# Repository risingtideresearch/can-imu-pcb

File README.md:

# CAN IMU

A carrier PCB for a Microstrain 3DM-CV7 Inertial Measurement Unit to act as a CAN / NMEA 2000
device.

It is designed to fit in the Hammond [1554E2GY](https://www.hammfg.com/part/1554E2GY) enclosure.

## Assembly

The BOM can be found [here](output/CAN_IMU_rev1_BOM.csv), and includes most parts, but there are
some additional parts not included there:

- The case: Hammond 1554E2GY
- Brass solderable nuts for securing the microstrain: SMTSOB-256-2ET (qty 3)
- M3x8 screws for securing the PCB in the enclosure (These should ideally be non-ferrous if you care about magnetemeter accuracy) 
- M12 connector: [T4130012051-000](https://www.digikey.com/en/products/detail/te-connectivity-amp-connectors/T4130012051-000/7927438)
- 5-pin PH connector housing for wiring the M12 to the board:
  [PHR-5](https://www.digikey.com/en/products/detail/jst-sales-america-inc/PHR-5/608605) (plus the
  appropriate crimp pins or pre-crimped wires)

## Software

Software for this board can be found in the [can-imu-fw repo](https://github.com/risingtideresearch/can-imu-fw)

# Revision History

## Rev 1

First fabricated January 2026. 

### Errata

- The microstrain IMU connector is backwards (repairable with cut traces and bodge wires)

## Rev 2

Fixes IMU connector pinout. No CPU pin changes, and functionally equivalent to bodged rev1.

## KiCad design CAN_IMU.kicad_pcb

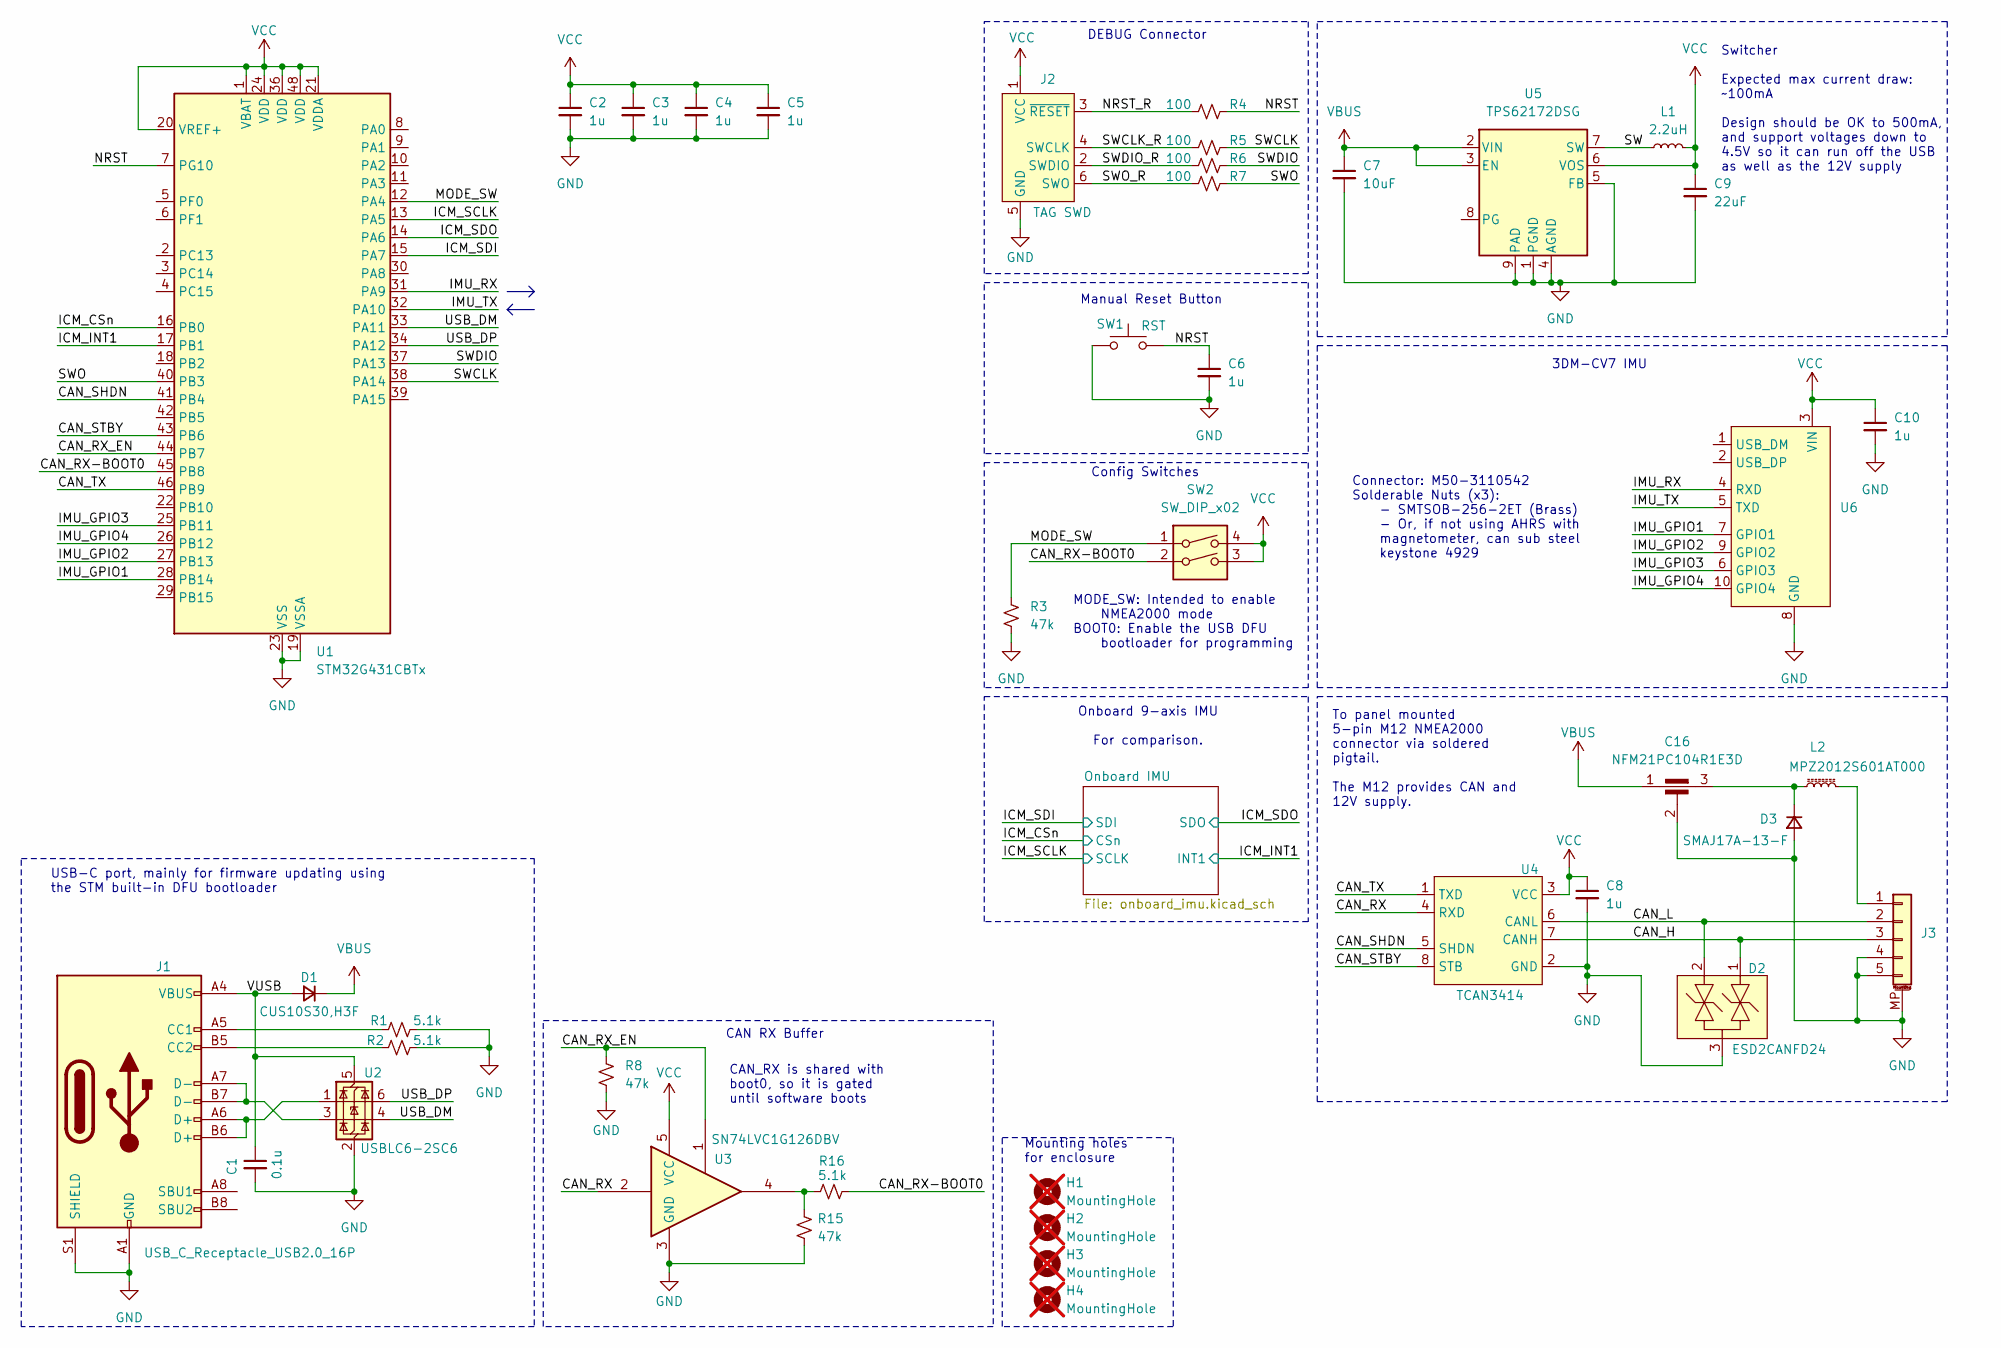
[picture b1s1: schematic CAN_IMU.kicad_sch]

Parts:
C1: 0.1u; C_0603_1608Metric; Mfg Part Number CL10B104KA8NNNC; LCSC Part Number C1590
C2, C3, C4, C5, C6, C8, C10: 1u; C_0603_1608Metric; Mfg Part Number CL10B105KP8NNNC; Digikey Part Number 1276-1946-1-ND
C7: 10uF; C_0805_2012Metric; Mfg Part Number GRM21BR61H106KE43L; Digikey Part Number 490-18663-1-ND
C9: 22uF; C_1206_3216Metric; Mfg Part Number CL31A226KAHNNNE; Digikey Part Number 1276-3047-1-ND
C16: NFM21PC104R1E3D; NFM21PC_Feedthrough_Cap; Mfg Part Number NFM21PC104R1E3D; LCSC Part Number C86150
D1: CUS10S30,H3F; D_SOD-323_HandSoldering; Mfg Part Number CUS10S30,H3F; Digikey Part Number CUS10S30H3FCT-ND
D2: ESD2CANFD24; SOT-23; Mfg Part Number ESD2CANFD24; Digikey Part Number 1727-PESD2CANFD24UU-QXCT-ND
D3: SMAJ17A-13-F; D_SMA; Mfg Part Number SMAJ17A-13-F; Digikey Part Number SMAJ17A-FDICT-ND
H1, H2, H3, H4: MountingHole; MountingHole_3.2mm_M3; not fitted
J1: USB_C_Receptacle_USB2.0_16P; USB_C_Receptacle_JAE_DX07S024WJ3R400; Mfg Part Number DX07S024WJ3R400; Digikey Part Number 670-2950-1-ND
J2: TAG SWD; Tag-Connect_TC2030-IDC-FP_2x03_P1.27mm_Vertical
J3: Conn_01x05; JST_PH_B5B-PH-SM4-TB_1x05-1MP_P2.00mm_Vertical; Mfg Part Number B5B-PH-SM4-TB; Digikey Part Number 455-B5B-PH-SM4-TBCT-ND
L1: 2.2uH; IND_LQH5BPN2R2NT0L; Mfg Part Number LQH5BPN2R2NT0L; Digikey Part Number 490-7778-1-ND
L2: MPZ2012S601AT000; L_0805_2012Metric; Mfg Part Number MPZ2012S601AT000; Digikey Part Number 445-MPZ2012S601AT000CT-ND
R1, R2, R16: 5.1k; R_0603_1608Metric; Mfg Part Number RC0603FR-075K1L; LCSC Part Number C105580
R3, R8, R15: 47k; R_0603_1608Metric; Mfg Part Number RC0603FR-0747KL; Digikey Part Number 311-47.0KHRCT-ND
R4, R5, R6, R7: 100; R_0603_1608Metric; Mfg Part Number RC0603FR-07100RL; Digikey Part Number 311-100HRCT-ND
SW1: RST; SW_SPST_PTS810; Mfg Part Number PTS810SJK250SMTRLFS; LCSC Part Number C221896
SW2: SW_DIP_x02; SW_DIP_SPSTx02_Slide_6.7x6.64mm_W8.61mm_P2.54mm_LowProfile; Mfg Part Number DS04-254-2-02BK-SMT-TR; Digikey Part Number 2223-DS04-254-2-02BK-SMT-CT-ND
U1: STM32G431CBTx; LQFP-48_7x7mm_P0.5mm; Mfg Part Number STM32G431CBT6; Digikey Part Number 497-19473-ND
U2: USBLC6-2SC6; SOT-23-6; Mfg Part Number USBLC6-2SC6; LCSC Part Number C7519
U3: SN74LVC1G126DBV; SOT-23-5; Mfg Part Number SN74LVC1G126DBVR; Digikey Part Number 296-11605-1-ND
U4: TCAN3414; SOIC-8_3.9x4.9mm_P1.27mm; Mfg Part Number TCAN3414DR; Digikey Part Number 296-TCAN3414DRCT-ND
U5: TPS62172DSG; WSON-8-1EP_2x2mm_P0.5mm_EP0.9x1.6mm_ThermalVias; Mfg Part Number TPS62172DSGR; Digikey Part Number 296-39449-1-ND
U6: 3DM-CV7; Mfg Part Number M50-3110542; Digikey Part Number 952-2342-ND

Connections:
/CAN_H: D2.1, J3.3, U4.7 (CANH)
/CAN_L: D2.2, J3.2, U4.6 (CANL)
/CAN_RX: U3.2, U4.4 (RXD)
/CAN_RX-BOOT0: R16.1, SW2.2, U1.45 (PB8)
/CAN_RX_EN: R8.1, U1.44 (PB7), U3.1
/CAN_SHDN: U1.41 (PB4), U4.5 (SHDN)
/CAN_STBY: U1.43 (PB6), U4.8 (STB)
/CAN_TX: U1.46 (PB9), U4.1 (TXD)
/ICM_CSn: U1.16 (PB0); also elsewhere on the board
/ICM_INT1: U1.17 (PB1); also elsewhere on the board
/ICM_SCLK: U1.13 (PA5); also elsewhere on the board
/ICM_SDI: U1.15 (PA7); also elsewhere on the board
/ICM_SDO: U1.14 (PA6); also elsewhere on the board
/IMU_GPIO1: U1.28 (PB14), U6.7 (GPIO1)
/IMU_GPIO2: U1.27 (PB13), U6.9 (GPIO2)
/IMU_GPIO3: U1.25 (PB11), U6.6 (GPIO3)
/IMU_GPIO4: U1.26 (PB12), U6.10 (GPIO4)
/IMU_RX: U1.31 (PA9), U6.4 (RXD)
/IMU_TX: U1.32 (PA10), U6.5 (TXD)
/MODE_SW: R3.1, SW2.1, U1.12 (PA4)
/NRST: C6.1, R4.1, SW1.2, U1.7 (PG10)
/NRST_R: J2.3 (~RESET), R4.2
/SW: L1.1, U5.7 (SW)
/SWCLK: R5.1, U1.38 (PA14)
/SWCLK_R: J2.4 (SWCLK), R5.2
/SWDIO: R6.1, U1.37 (PA13)
/SWDIO_R: J2.2 (SWDIO), R6.2
/SWO: R7.1, U1.40 (PB3)
/SWO_R: J2.6 (SWO), R7.2
/USB_DM: U1.33 (PA11), U2.4 (I/O2)
/USB_DP: U1.34 (PA12), U2.6 (I/O1)
/VUSB: C1.1, D1.2 (A), J1.A4 (VBUS), J1.A9 (VBUS), J1.B4 (VBUS), J1.B9 (VBUS), U2.5 (VBUS)
GND: C1.2, C2.2, C3.2, C4.2, C5.2, C6.2, C7.2, C8.2, C9.2, C10.2, C16.2, D2.3, D3.2 (A), J1.A1 (GND), J1.A12 (GND), J1.B1 (GND), J1.B12 (GND), J1.S1 (SHIELD), J2.5 (GND), J3.4, J3.5, J3.MP (MountPin), R1.1, R2.1, R3.2, R8.2, R15.2, SW1.1, U1.19 (VSSA), U1.23 (VSS), U1.35 (VSS), U1.47 (VSS), U2.2 (GND), U3.3 (GND), U4.2 (GND), U5.1 (PGND), U5.4 (AGND), U5.5 (FB), U5.9 (PAD), U6.8 (GND); also elsewhere on the board
unnamed: C16.3, D3.1 (K), L2.1
unnamed: J1.A5 (CC1), R1.2
unnamed: J1.B5 (CC2), R2.2
unnamed: J1.A6 (D+), J1.B6 (D+), U2.1 (I/O1)
unnamed: J1.A7 (D-), J1.B7 (D-), U2.3 (I/O2)
unnamed: J3.1, L2.2
unnamed: R15.1, R16.2, U3.4
VBUS: C7.1, C16.1, D1.1 (K), U5.2 (VIN), U5.3 (EN)
VCC: C2.1, C3.1, C4.1, C5.1, C8.1, C9.1, C10.1, J2.1 (VCC), L1.2, SW2.3, SW2.4, U1.1 (VBAT), U1.20 (VREF+), U1.21 (VDDA), U1.24 (VDD), U1.36 (VDD), U1.48 (VDD), U3.5 (VCC), U4.3 (VCC), U5.6 (VOS), U6.3 (VIN); also elsewhere on the board

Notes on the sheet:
DEBUG Connector
Mounting holes for enclosure
To panel mounted 5-pin M12 NMEA2000 connector via soldered pigtail. The M12 provides CAN and 12V supply.
Connector: M50-3110542 Solderable Nuts (x3): - SMTSOB-256-2ET (Brass) - Or, if not using AHRS with magnetometer, can sub steel keystone 4929
CAN RX Buffer
3DM-CV7 IMU
Manual Reset Button
Onboard 9-axis IMU For comparison.
CAN_RX is shared with boot0, so it is gated until software boots
MODE_SW: Intended to enable NMEA2000 mode BOOT0: Enable the USB DFU bootloader for programming
Switcher Expected max current draw: ~100mA Design should be OK to 500mA, and support voltages down to 4.5V so it can run off the USB as well as the 12V supply
USB-C port, mainly for firmware updating using the STM built-in DFU bootloader
Config Switches

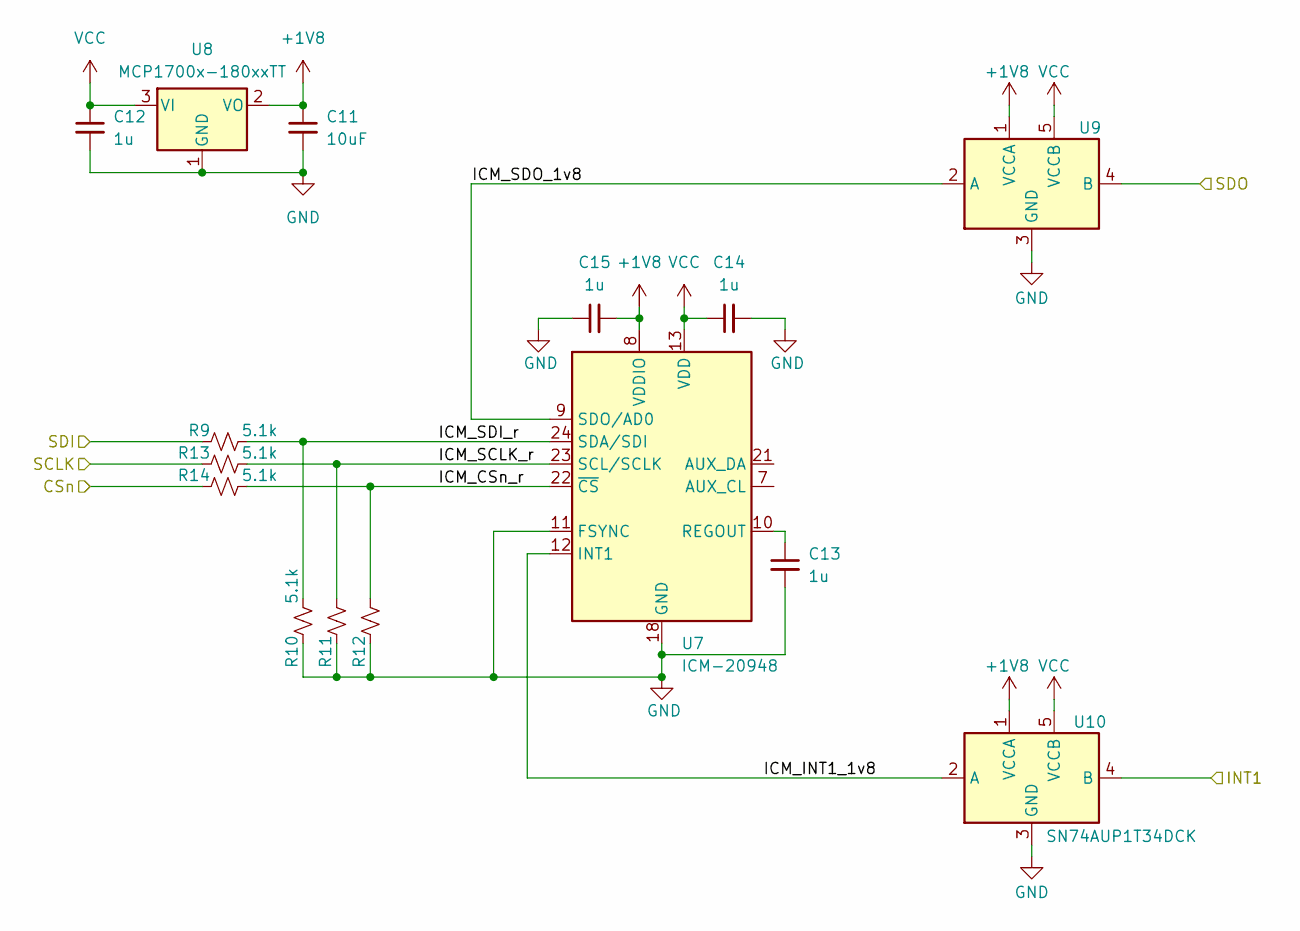
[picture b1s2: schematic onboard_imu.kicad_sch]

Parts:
C11: 10uF; C_0805_2012Metric; Mfg Part Number GRM21BR61H106KE43L; Digikey Part Number 490-18663-1-ND
C12, C13, C14, C15: 1u; C_0603_1608Metric; Mfg Part Number CL10B105KP8NNNC; Digikey Part Number 1276-1946-1-ND
R9, R10, R11, R12, R13, R14: 5.1k; R_0603_1608Metric; Mfg Part Number RC0603FR-075K1L; LCSC Part Number C105580
U7: ICM-20948; InvenSense_QFN-24_3x3mm_P0.4mm; Mfg Part Number ICM-20948; Digikey Part Number 1428-1123-1-ND
U8: MCP1700x-180xxTT; SOT-23; Mfg Part Number MCP1700T-1802E/TT; Digikey Part Number MCP1700T1802ETTCT-ND
U9, U10: SN74AUP1T34DCK; SOT-353_SC-70-5; Mfg Part Number SN74AUP1T34DCKR; Digikey Part Number 296-34900-1-ND

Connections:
+1V8: C11.1, C15.2, U7.8 (VDDIO), U8.2 (VO), U9.1 (VCCA), U10.1 (VCCA)
/ICM_CSn: R14.2; also elsewhere on the board
/ICM_INT1: U10.4 (B); also elsewhere on the board
/ICM_SCLK: R13.2; also elsewhere on the board
/ICM_SDI: R9.2; also elsewhere on the board
/ICM_SDO: U9.4 (B); also elsewhere on the board
/Onboard IMU/ICM_CSn_r: R12.1, R14.1, U7.22 (~CS)
/Onboard IMU/ICM_INT1_1v8: U7.12 (INT1), U10.2 (A)
/Onboard IMU/ICM_SCLK_r: R11.1, R13.1, U7.23 (SCL/SCLK)
/Onboard IMU/ICM_SDI_r: R9.1, R10.1, U7.24 (SDA/SDI)
/Onboard IMU/ICM_SDO_1v8: U7.9 (SDO/AD0), U9.2 (A)
GND: C11.2, C12.2, C13.2, C14.2, C15.1, R10.2, R11.2, R12.2, U7.11 (FSYNC), U7.18 (GND), U7.20 (GND), U8.1 (GND), U9.3 (GND), U10.3 (GND); also elsewhere on the board
unnamed: C13.1, U7.10 (REGOUT)
VCC: C12.1, C14.1, U7.13 (VDD), U8.3 (VI), U9.5 (VCCB), U10.5 (VCCB); also elsewhere on the board

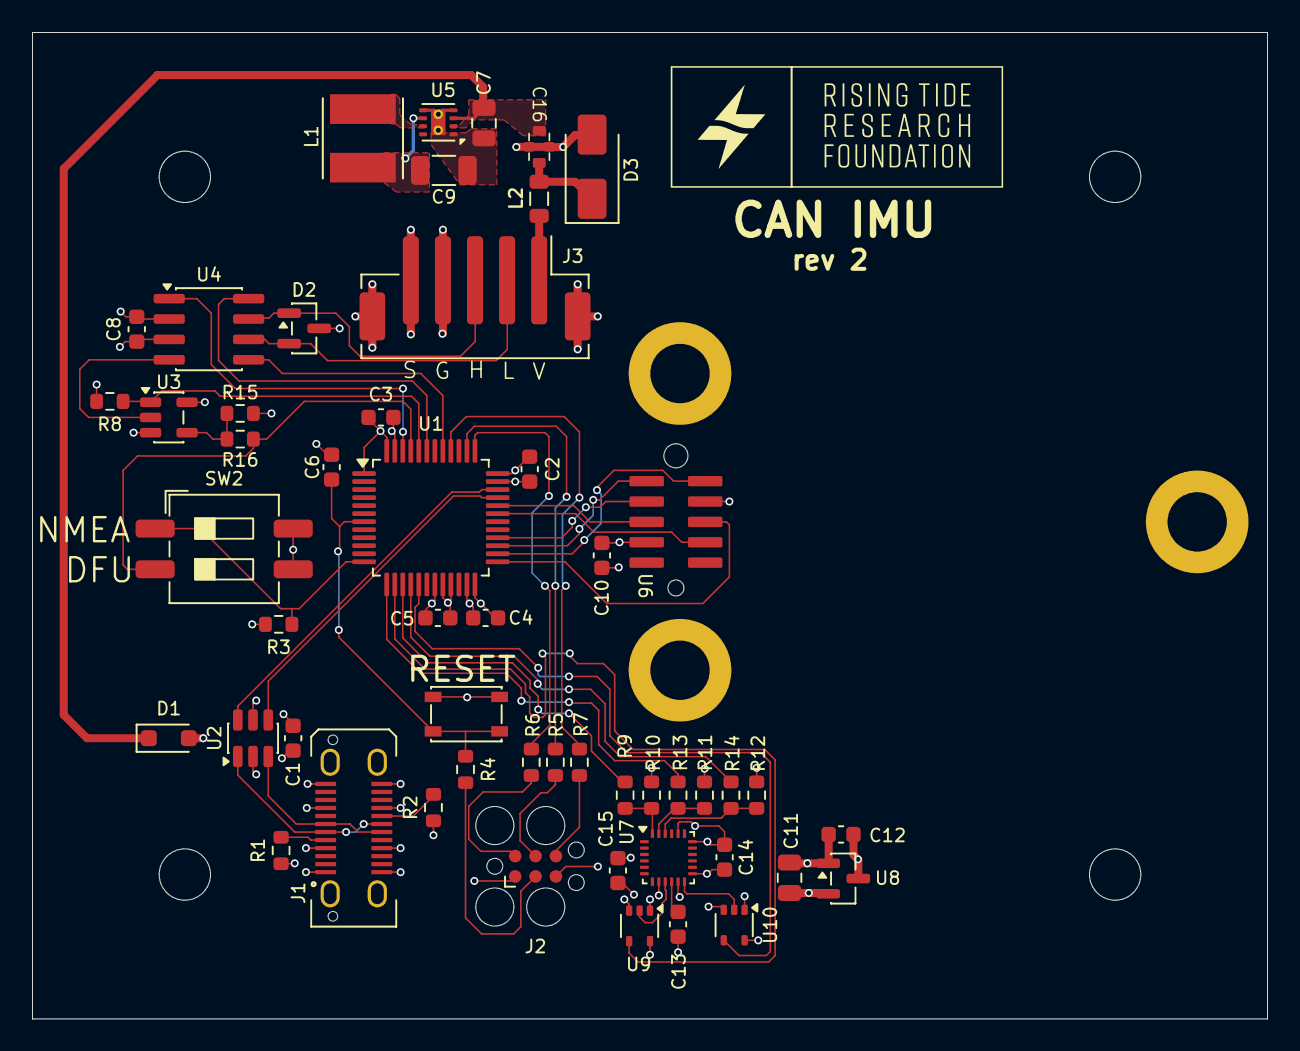
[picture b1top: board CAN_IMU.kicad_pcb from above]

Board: 4 copper layers, 77.0 x 61.5 mm, 56 parts (0 on the bottom side), 49 nets.

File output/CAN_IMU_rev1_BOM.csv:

"Reference","Qty","Value","DNP","Footprint","Mfg Part Number","Digikey Part Number","LCSC Part Number"
"C1","1","0.1u","","Capacitor_SMD:C_0603_1608Metric","CL10B104KA8NNNC","1276-1006-1-ND","C1590"
"C2-C6,C8,C10,C12-C15","11","1u","","Capacitor_SMD:C_0603_1608Metric","CL10B105KP8NNNC","1276-1946-1-ND","C15849"
"C7,C11","2","10uF","","Capacitor_SMD:C_0805_2012Metric","GRM21BR61H106KE43L","490-18663-1-ND","C15850"
"C9","1","22uF","","Capacitor_SMD:C_1206_3216Metric","CL31A226KAHNNNE","1276-3047-1-ND","C12891"
"C16","1","NFM21PC104R1E3D","","RJMP_Misc:NFM21PC_Feedthrough_Cap","NFM21PC104R1E3D","","C86150"
"D1","1","CUS10S30,H3F","","Diode_SMD:D_SOD-323_HandSoldering","CUS10S30,H3F","CUS10S30H3FCT-ND","C146335"
"D2","1","ESD2CANFD24","","Package_TO_SOT_SMD:SOT-23","ESD2CANFD24","1727-PESD2CANFD24UU-QXCT-ND","C5278878"
"D3","1","SMAJ17A-13-F","","Diode_SMD:D_SMA","SMAJ17A-13-F","SMAJ17A-FDICT-ND","C134963"
"J1","1","USB_C_Receptacle_USB2.0_16P","","Connector_USB:USB_C_Receptacle_JAE_DX07S024WJ3R400","DX07S024WJ3R400","670-2950-1-ND","C2896636"
"J3","1","Conn_01x05","","Connector_JST:JST_PH_B5B-PH-SM4-TB_1x05-1MP_P2.00mm_Vertical","B5B-PH-SM4-TB","455-B5B-PH-SM4-TBCT-ND","C265085"
"L1","1","2.2uH","","RJMP_Inductors:IND_LQH5BPN2R2NT0L","LQH5BPN2R2NT0L","490-7778-1-ND","C135262"
"L2","1","MPZ2012S601AT000","","Inductor_SMD:L_0805_2012Metric","MPZ2012S601AT000","445-MPZ2012S601AT000CT-ND","C21519"
"R1,R2,R9-R14,R16","9","5.1k","","Resistor_SMD:R_0603_1608Metric","RC0603FR-075K1L","311-5.10KHRCT-ND","C105580"
"R3,R8,R15","3","47k","","Resistor_SMD:R_0603_1608Metric","RC0603FR-0747KL","311-47.0KHRCT-ND","C25819"
"R4-R7","4","100","","Resistor_SMD:R_0603_1608Metric","RC0603FR-07100RL","311-100HRCT-ND","C105588"
"SW1","1","RST","","Button_Switch_SMD:SW_SPST_PTS810","PTS810SJK250SMTRLFS","CKN10503CT-ND","C221896"
"SW2","1","SW_DIP_x02","","Button_Switch_SMD:SW_DIP_SPSTx02_Slide_6.7x6.64mm_W8.61mm_P2.54mm_LowProfile","DS04-254-2-02BK-SMT-TR","2223-DS04-254-2-02BK-SMT-CT-ND","C3312524"
"U1","1","STM32G431CBTx","","Package_QFP:LQFP-48_7x7mm_P0.5mm","STM32G431CBT6","497-19473-ND","C529355"
"U2","1","USBLC6-2SC6","","Package_TO_SOT_SMD:SOT-23-6","USBLC6-2SC6","497-5235-1-ND","C7519"
"U3","1","SN74LVC1G126DBV","","Package_TO_SOT_SMD:SOT-23-5","SN74LVC1G126DBVR","296-11605-1-ND","C46472327"
"U4","1","TCAN3414","","Package_SO:SOIC-8_3.9x4.9mm_P1.27mm","TCAN3414DR","296-TCAN3414DRCT-ND","C22396693"
"U5","1","TPS62172DSG","","Package_SON:WSON-8-1EP_2x2mm_P0.5mm_EP0.9x1.6mm_ThermalVias","TPS62172DSGR","296-39449-1-ND","C59873"
"U6","1","~","","RJMP_Connectors:3DM-CV7","M50-3110542","952-2342-ND","C6659241"
"U7,U8","2","ICM-20948,MCP1700x-180xxTT","","Package_TO_SOT_SMD:SOT-23,Sensor_Motion:InvenSense_QFN-24_3x3mm_P0.4mm","","",""
"U9,U10","2","SN74AUP1T34DCK","","Package_TO_SOT_SMD:SOT-353_SC-70-5","SN74AUP1T34DCKR","296-34900-1-ND",""

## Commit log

2025-12-17 Schematic more or less complete
2025-12-17 Add pulldown to CAN_RX_EN
2025-12-17 Basically finished layout
2025-12-17 Add 3D models for connectors
2025-12-23 Add part numbers and output generation
2025-12-24 Add onboard IMU and logo
2026-01-02 Add pull-down and series resistor to CAN_RX
    Prevent shorting the buffer output when throwing the DIP switch
2026-01-02 Add rev1 output files
2026-01-20 Fix some missing part numbers and update BOM
    No artwork changes.
2026-01-20 Add extra parts to README
2026-02-19 Update README.md
    Add Rev1 errata note
2026-03-11 Rev 2 updates
    - Fix microstrain connector pinout
    - Update silkscreen rev
2026-03-12 Fix DRC errors
    - Move refdes for moved capacitor
2026-03-12 rev2 outputs
2026-03-12 Update README for rev2
2026-03-13 Add photo
